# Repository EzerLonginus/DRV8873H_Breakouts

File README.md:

# DRV8873H_Breakouts
DRV8873H Breakouts for internal development

## Scematic

## Layout

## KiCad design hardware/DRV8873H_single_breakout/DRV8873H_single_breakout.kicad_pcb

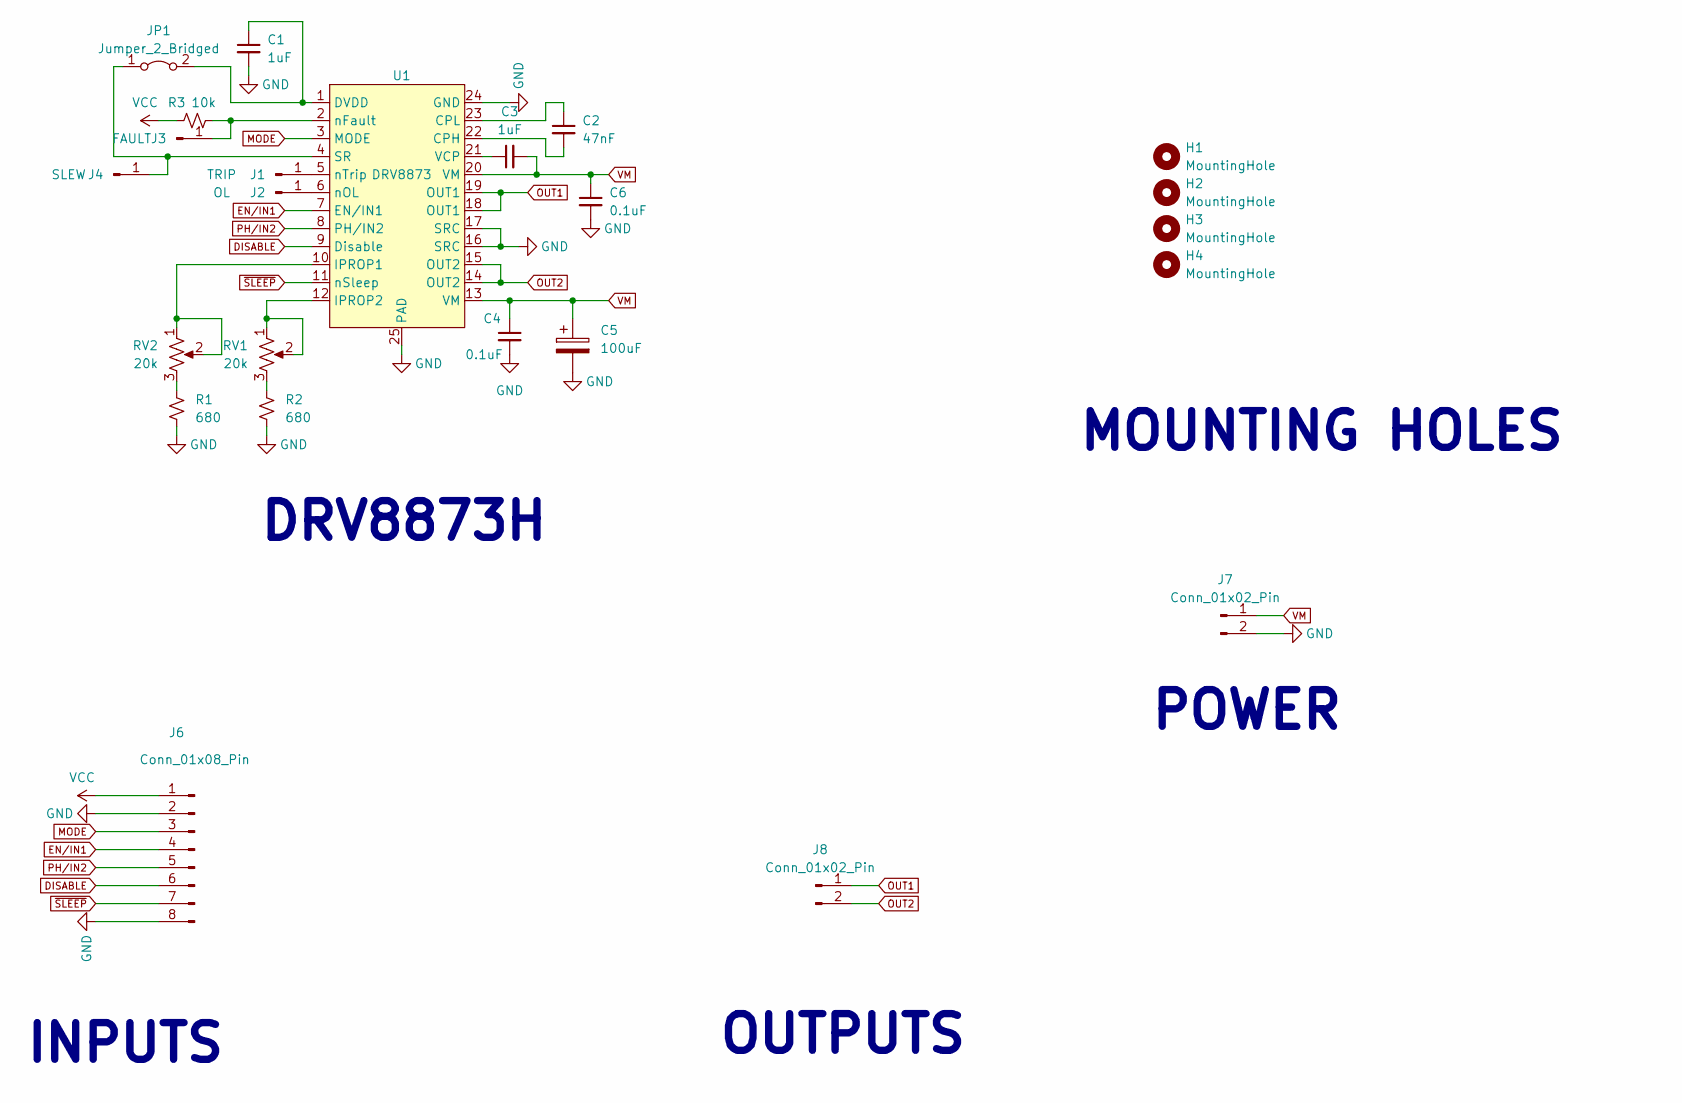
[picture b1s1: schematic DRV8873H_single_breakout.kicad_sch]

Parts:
C1, C3: 1uF; C_0603_1608Metric_Pad1.08x0.95mm_HandSolder
C2: 47nF; C_0603_1608Metric_Pad1.08x0.95mm_HandSolder
C4, C6: 0.1uF; C_0603_1608Metric_Pad1.08x0.95mm_HandSolder
C5: 100uF; C_1210_3225Metric_Pad1.33x2.70mm_HandSolder
H1, H2, H3, H4: MountingHole; MountingHole_3.2mm_M3
J1: TRIP; PinHeader_1x01_P2.54mm_Vertical
J2: OL; PinHeader_1x01_P2.54mm_Vertical
J3: FAULT; PinHeader_1x01_P2.54mm_Vertical
J4: SLEW; PinHeader_1x01_P2.54mm_Vertical
J6: Conn_01x08_Pin; TerminalBlock_4Ucon_1x08_P3.50mm_Horizontal
J7, J8: Conn_01x02_Pin; TerminalBlock_bornier-2_P5.08mm
JP1: Jumper_2_Bridged; SolderJumper-2_P1.3mm_Bridged_Pad1.0x1.5mm
R1, R2: 680; R_0603_1608Metric_Pad0.98x0.95mm_HandSolder
R3: 10k; R_0603_1608Metric_Pad0.98x0.95mm_HandSolder
RV1, RV2: 20k; Potentiometer_Bourns_3266Y_Vertical
U1: DRV8873; HTSSOP-24-1EP_4.4x7.8mm_P0.65mm_EP3.4x7.8mm_Mask2.4x2.98mm

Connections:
DISABLE: J6.6, U1.9 (Disable)
EN/IN1: J6.4, U1.7 (EN/IN1)
GND: C1.2, C4.2, C5.2, C6.2, J6.2, J6.8, J7.2, R1.2, R2.2, U1.16 (SRC), U1.17 (SRC), U1.24 (GND), U1.25 (PAD)
MODE: J6.3, U1.3 (MODE)
unnamed: J1.1, U1.5 (nTrip)
unnamed: J2.1, U1.6 (nOL)
unnamed: J3.1, R3.2, U1.2 (nFault)
unnamed: J4.1, JP1.1 (A), U1.4 (SR)
unnamed: C1.1, JP1.2 (B), U1.1 (DVDD)
unnamed: R1.1, RV2.3
unnamed: R2.1, RV1.3
unnamed: C2.2, U1.22 (CPH)
unnamed: C2.1, U1.23 (CPL)
unnamed: RV2.1, RV2.2, U1.10 (IPROP1)
unnamed: RV1.1, RV1.2, U1.12 (IPROP2)
unnamed: C3.1, U1.21 (VCP)
OUT1: J8.1, U1.18 (OUT1), U1.19 (OUT1)
OUT2: J8.2, U1.14 (OUT2), U1.15 (OUT2)
PH/IN2: J6.5, U1.8 (PH/IN2)
VCC: J6.1, R3.1
VM: C3.2, C4.1, C5.1, C6.1, J7.1, U1.13 (VM), U1.20 (VM)
~SLEEP: J6.7, U1.11 (nSleep)

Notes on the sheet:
MOUNTING HOLES
INPUTS
POWER
OUTPUTS
DRV8873H

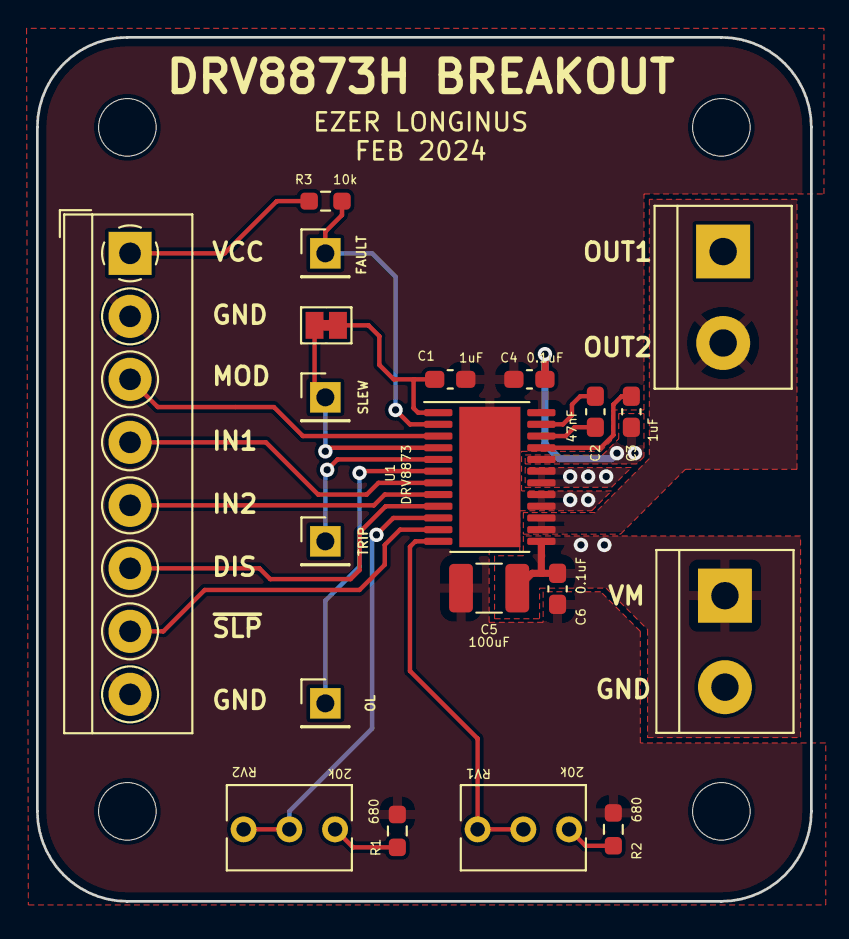
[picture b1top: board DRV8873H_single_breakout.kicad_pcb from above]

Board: 2 copper layers, 43.0 x 48.0 mm, 24 parts (0 on the bottom side), 22 nets.

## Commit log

2024-02-09 Initial Design Files
